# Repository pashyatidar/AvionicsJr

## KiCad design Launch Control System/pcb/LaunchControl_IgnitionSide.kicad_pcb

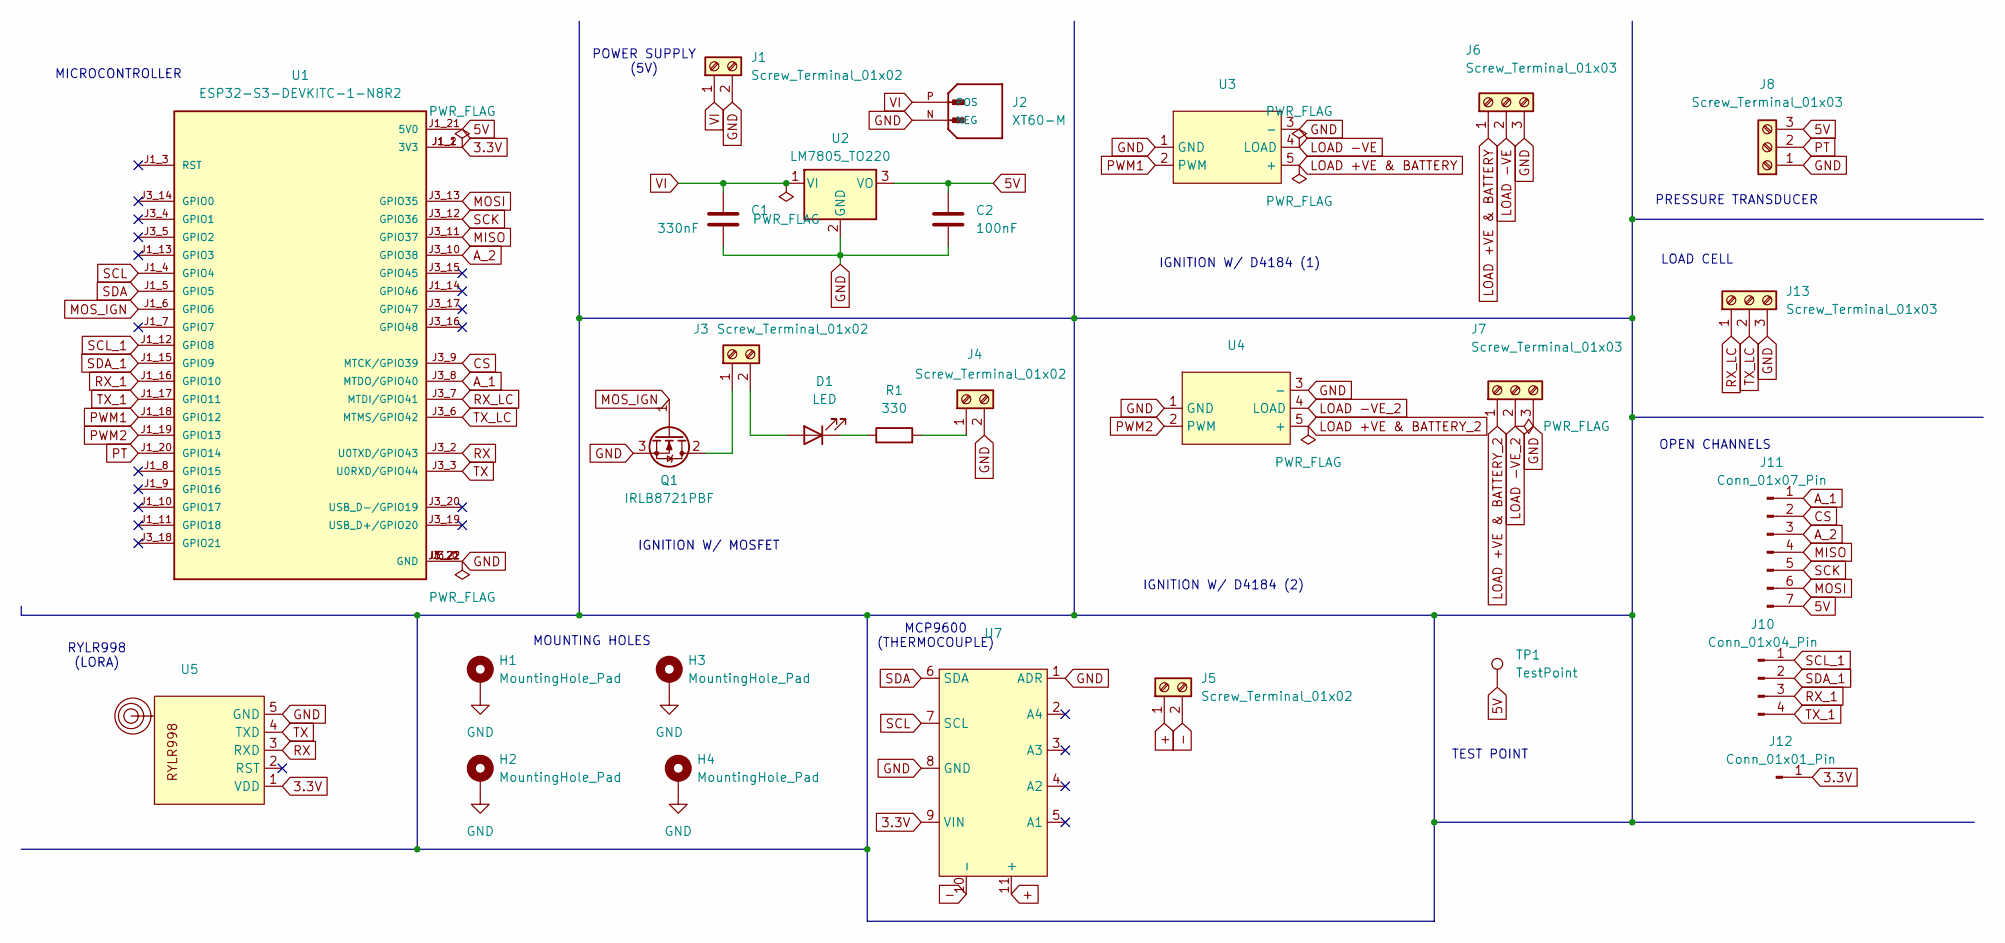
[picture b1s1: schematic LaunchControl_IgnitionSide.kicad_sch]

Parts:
C1: 330nF; C_0805_2012Metric
C2: 100nF; C_0805_2012Metric
D1: LED; LED_0805_2012Metric
H1, H2, H3, H4: MountingHole_Pad; MountingHole_4.3mm_M4_DIN965_Pad
J1, J3, J4, J5: Screw_Terminal_01x02; TerminalBlock_bornier-2_P5.08mm
J2: XT60-M; AMASS_XT60-M; PARTREV V1.2
J6, J7, J8, J13: Screw_Terminal_01x03; TerminalBlock_bornier-3_P5.08mm
J10: Conn_01x04_Pin; PinHeader_1x04_P2.54mm_Vertical
J11: Conn_01x07_Pin; PinHeader_1x07_P2.54mm_Vertical
J12: Conn_01x01_Pin; PinHeader_1x01_P2.54mm_Vertical
Q1: IRLB8721PBF; TO-220-3_Vertical
R1: 330; R_0805_2012Metric
TP1: TestPoint; TestPoint_Loop_D2.60mm_Drill1.6mm_Beaded
U1: ESP32-S3-DEVKITC-1-N8R2; XCVR_ESP32-S3-DEVKITC-1-N8R2; PARTREV V1
U2: LM7805_TO220; TO-220-3_Vertical
U3, U4: D4184
U5: RYLR998
U7: MCP9600

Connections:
3.3V: J12.1, U1.J1_1 (3V3), U1.J1_2 (3V3), U5.1 (VDD), U7.9 (VIN)
5V: C2.2, J8.3, J11.7, TP1.1, U1.J1_21 (5V0), U2.3 (VO)
+: J5.1, U7.11 (+)
-: J5.2, U7.10 (-)
A_1: J11.1, U1.J3_8 (MTDO/GPIO40)
A_2: J11.3, U1.J3_10 (GPIO38)
CS: J11.2, U1.J3_9 (MTCK/GPIO39)
GND: C1.1, C2.1, H1.1, H2.1, H3.1, H4.1, J1.2, J2.N (NEG), J4.2, J6.3, J7.3, J8.1, J13.3, Q1.3 (S), U1.J1_22 (GND), U1.J3_1 (GND), U1.J3_21 (GND), U1.J3_22 (GND), U2.2 (GND), U3.1 (GND), U3.3 (-), U4.1 (GND), U4.3 (-), U5.5 (GND), U7.1 (ADR), U7.8 (GND)
LOAD +VE & BATTERY: J6.1, U3.5 (+)
LOAD +VE & BATTERY_2: J7.1, U4.5 (+)
LOAD -VE: J6.2, U3.4 (LOAD)
LOAD -VE_2: J7.2, U4.4 (LOAD)
MISO: J11.4, U1.J3_11 (GPIO37)
MOSI: J11.6, U1.J3_13 (GPIO35)
MOS_IGN: Q1.1 (G), U1.J1_6 (GPIO6)
unnamed: D1.2 (A), J3.2
unnamed: D1.1 (K), R1.1
unnamed: J3.1, Q1.2 (D)
unnamed: J4.1, R1.2
PT: J8.2, U1.J1_20 (GPIO14)
PWM1: U1.J1_18 (GPIO12), U3.2 (PWM)
PWM2: U1.J1_19 (GPIO13), U4.2 (PWM)
RX: U1.J3_2 (U0TXD/GPIO43), U5.3 (RXD)
RX_1: J10.3, U1.J1_16 (GPIO10)
RX_LC: J13.1, U1.J3_7 (MTDI/GPIO41)
SCK: J11.5, U1.J3_12 (GPIO36)
SCL: U1.J1_4 (GPIO4), U7.7 (SCL)
SCL_1: J10.1, U1.J1_12 (GPIO8)
SDA: U1.J1_5 (GPIO5), U7.6 (SDA)
SDA_1: J10.2, U1.J1_15 (GPIO9)
TX: U1.J3_3 (U0RXD/GPIO44), U5.4 (TXD)
TX_1: J10.4, U1.J1_17 (GPIO11)
TX_LC: J13.2, U1.J3_6 (MTMS/GPIO42)
VI: C1.2, J1.1, J2.P (POS), U2.1 (VI)

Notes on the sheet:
PRESSURE TRANSDUCER
LOAD CELL
IGNITION W/ D4184 (2)
RYLR998 (LORA)
OPEN CHANNELS
IGNITION W/ D4184 (1)
POWER SUPPLY (5V)
IGNITION W/ MOSFET
MOUNTING HOLES
MICROCONTROLLER
MCP9600 (THERMOCOUPLE)
TEST POINT

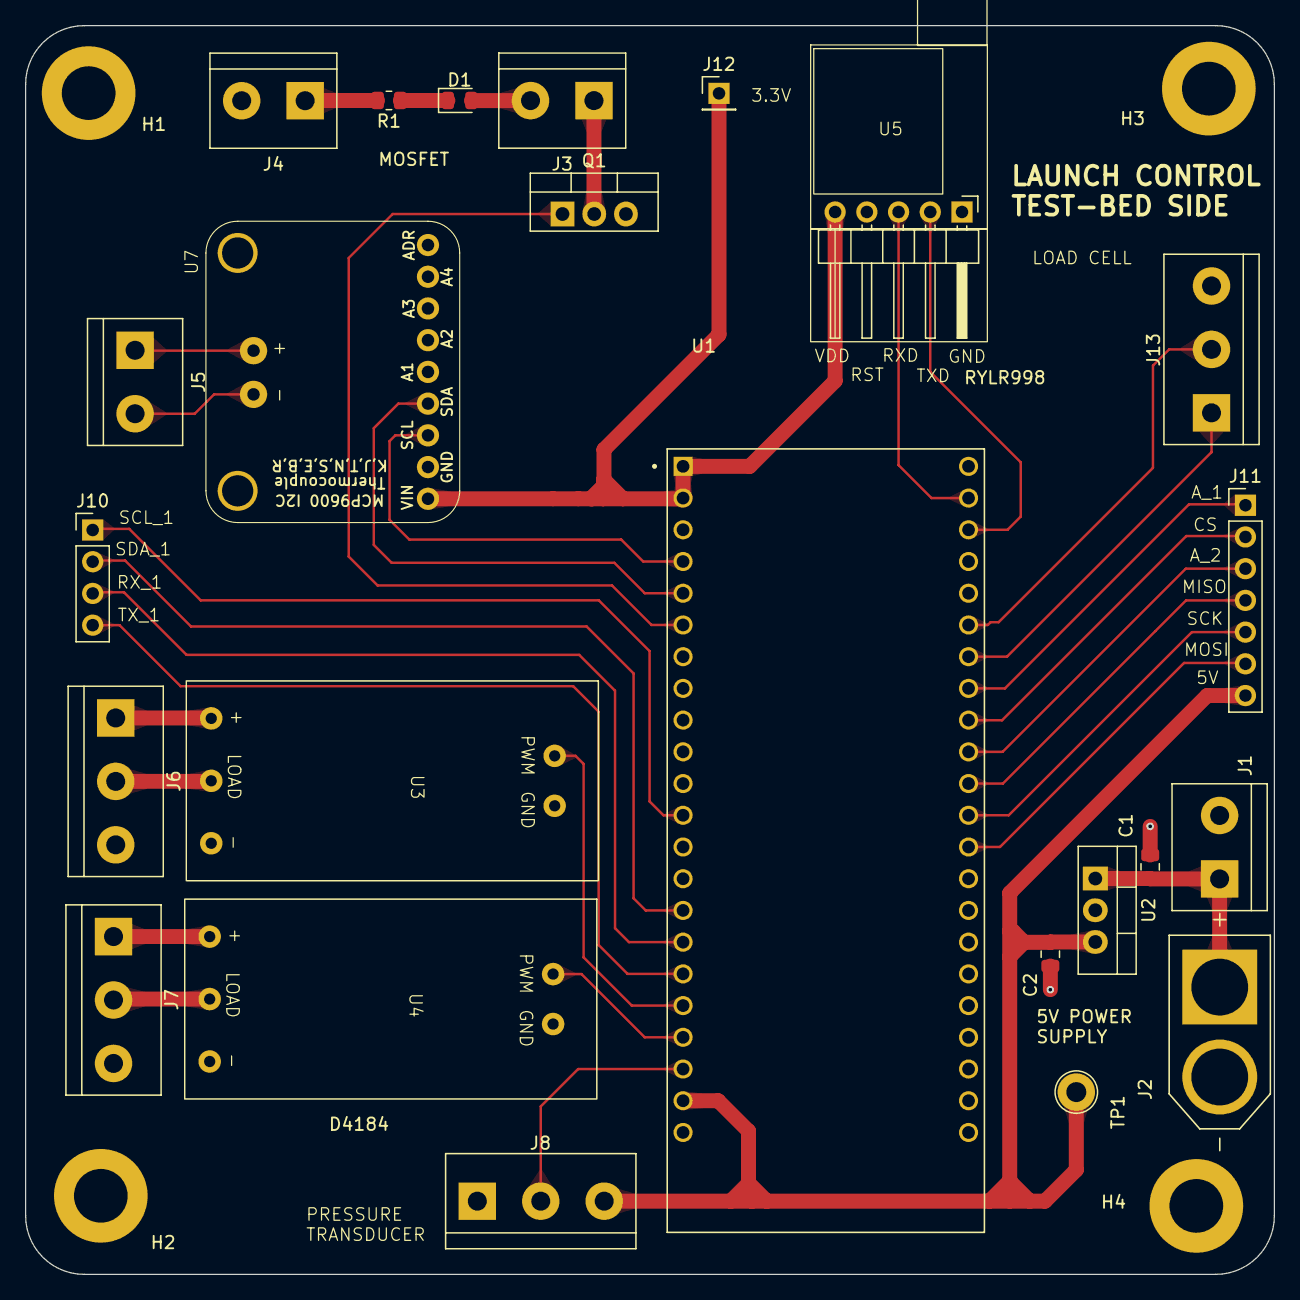
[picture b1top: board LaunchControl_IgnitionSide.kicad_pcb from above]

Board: 2 copper layers, 100.0 x 100.0 mm, 28 parts (0 on the bottom side), 34 nets.

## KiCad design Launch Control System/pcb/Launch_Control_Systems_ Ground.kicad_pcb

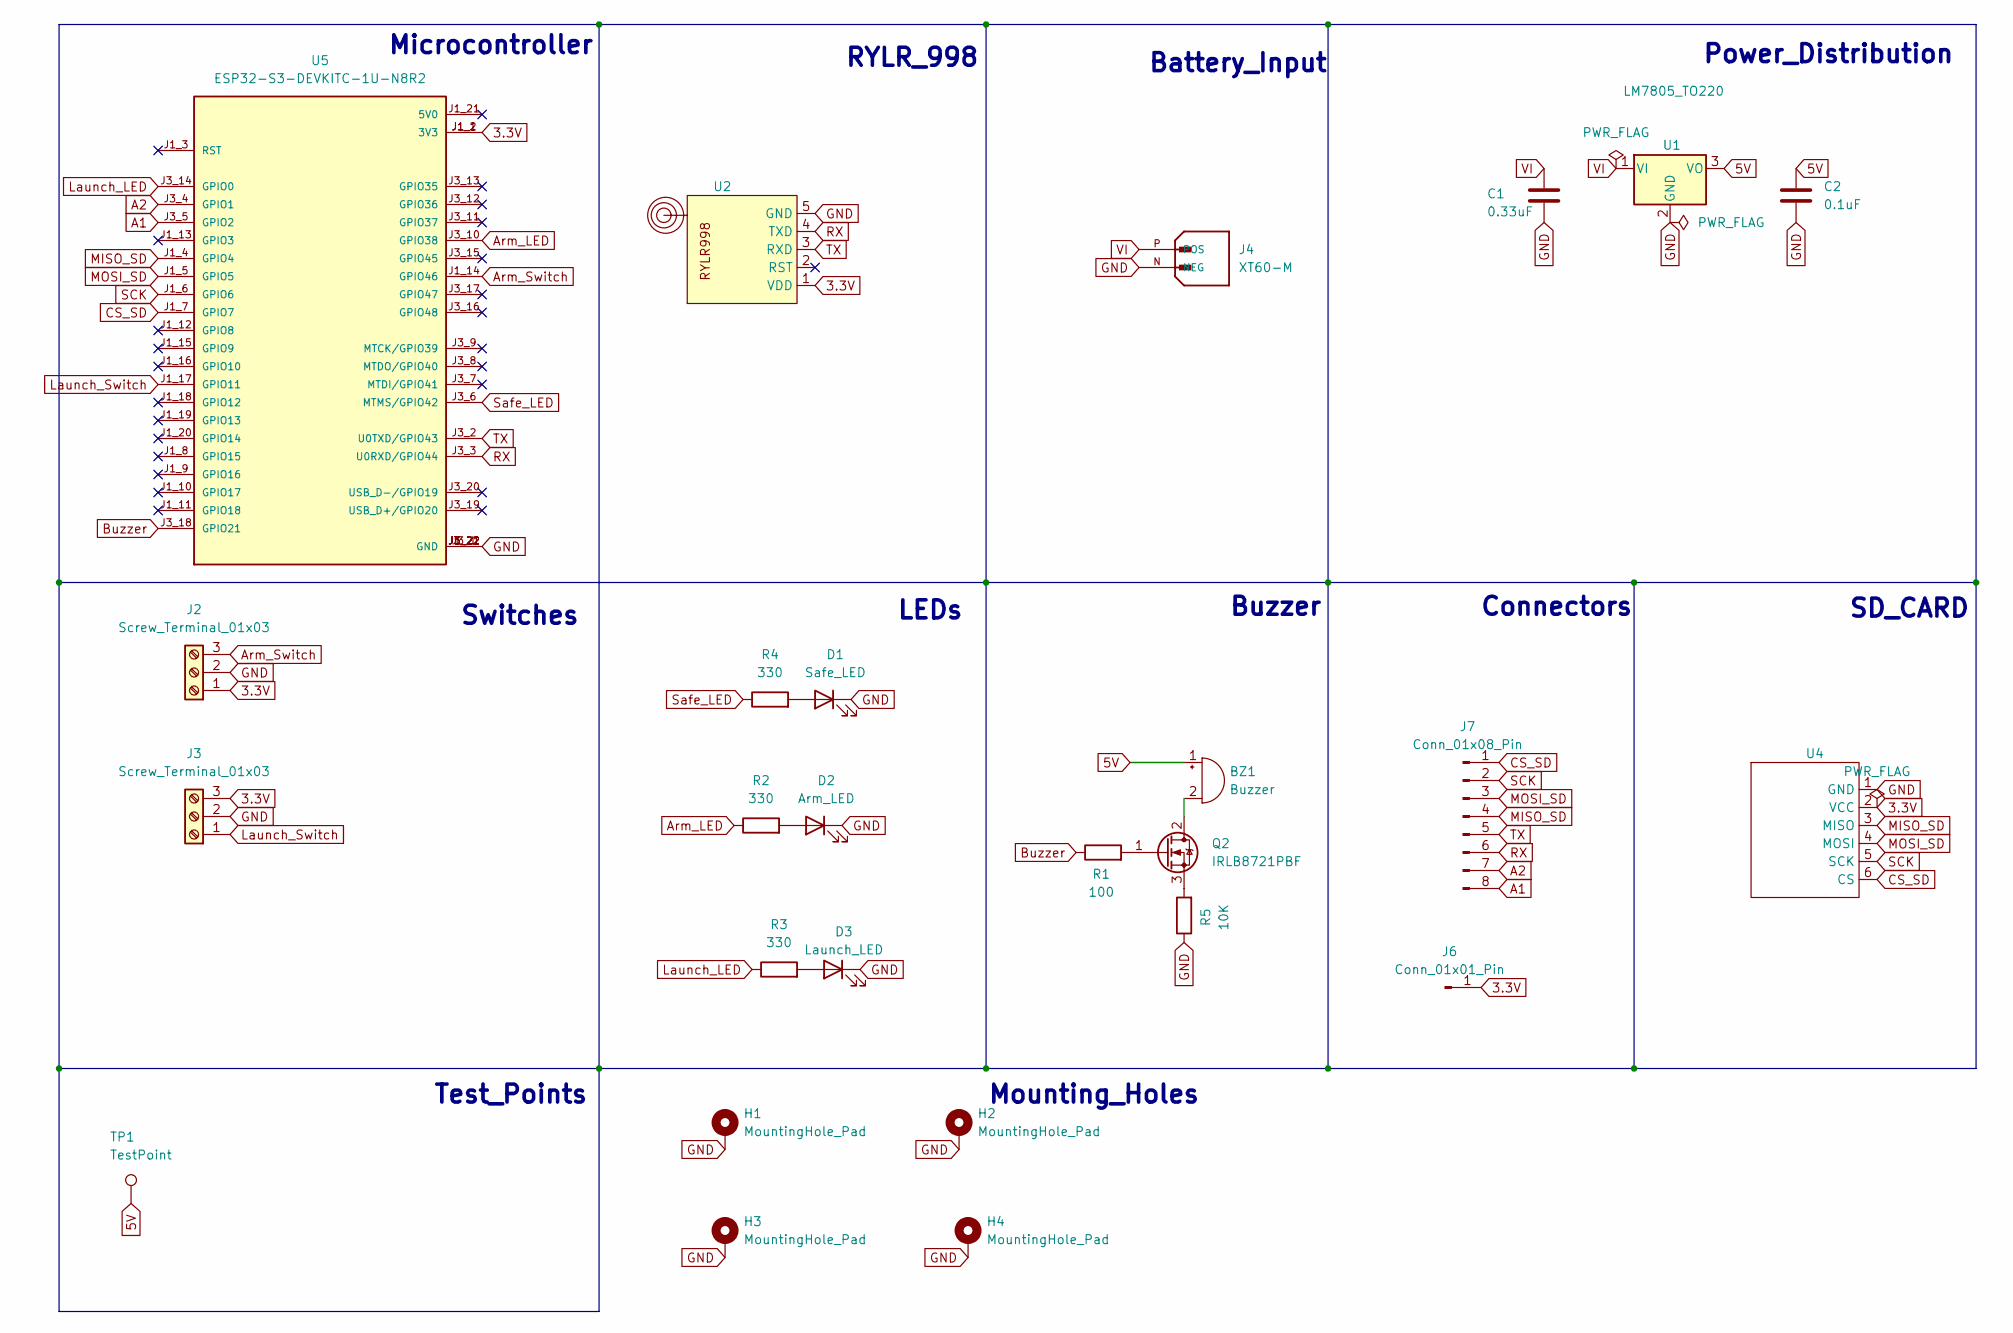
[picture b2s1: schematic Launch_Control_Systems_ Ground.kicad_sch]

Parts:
BZ1: Buzzer; Buzzer_12x9.5RM7.6
C1: 0.33uF; C_0805_2012Metric
C2: 0.1uF; C_0805_2012Metric
D1: Safe_LED; LED_D5.0mm
D2: Arm_LED; LED_D5.0mm
D3: Launch_LED; LED_D5.0mm
H1, H2, H3, H4: MountingHole_Pad; MountingHole_4.3mm_M4_DIN965_Pad
J2, J3: Screw_Terminal_01x03; TerminalBlock_bornier-3_P5.08mm
J4: XT60-M; AMASS_XT60-M; PARTREV V1.2
J6: Conn_01x01_Pin; PinHeader_1x01_P2.54mm_Vertical
J7: Conn_01x08_Pin; PinHeader_1x08_P2.54mm_Vertical
Q2: IRLB8721PBF; TO-220-3_Vertical
R1: 100; R_0805_2012Metric
R2, R3, R4: 330; R_0805_2012Metric
R5: 10K; R_0805_2012Metric
TP1: TestPoint; TestPoint_Loop_D2.60mm_Drill1.6mm_Beaded
U1: LM7805_TO220; TO-220-3_Vertical
U2: RYLR_998_SKT
U4: SD card reader 2
U5: ESP32-S3-DEVKITC-1U-N8R2; XCVR_ESP32-S3-DEVKITC-1U-N8R2

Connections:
3.3V: J2.1, J3.3, J6.1, U2.1 (VDD), U4.2 (VCC), U5.J1_1 (3V3), U5.J1_2 (3V3)
5V: BZ1.1 (+), C2.1, TP1.1, U1.3 (VO)
A1: J7.8, U5.J3_5 (GPIO2)
A2: J7.7, U5.J3_4 (GPIO1)
Arm_LED: R2.1, U5.J3_10 (GPIO38)
Arm_Switch: J2.3, U5.J1_14 (GPIO46)
Buzzer: R1.1, U5.J3_18 (GPIO21)
CS_SD: J7.1, U4.6 (CS), U5.J1_7 (GPIO7)
GND: C1.2, C2.2, D1.1 (K), D2.1 (K), D3.1 (K), H1.1, H2.1, H3.1, H4.1, J2.2, J3.2, J4.N (NEG), R5.1, U1.2 (GND), U2.5 (GND), U4.1 (GND), U5.J1_22 (GND), U5.J3_1 (GND), U5.J3_21 (GND), U5.J3_22 (GND)
Launch_LED: R3.1, U5.J3_14 (GPIO0)
Launch_Switch: J3.1, U5.J1_17 (GPIO11)
MISO_SD: J7.4, U4.3 (MISO), U5.J1_4 (GPIO4)
MOSI_SD: J7.3, U4.4 (MOSI), U5.J1_5 (GPIO5)
unnamed: BZ1.2 (-), Q2.2 (D)
unnamed: D1.2 (A), R4.2
unnamed: D2.2 (A), R2.2
unnamed: D3.2 (A), R3.2
unnamed: Q2.1 (G), R1.2
unnamed: Q2.3 (S), R5.2
RX: J7.6, U2.4 (TXD), U5.J3_3 (U0RXD/GPIO44)
SCK: J7.2, U4.5 (SCK), U5.J1_6 (GPIO6)
Safe_LED: R4.1, U5.J3_6 (MTMS/GPIO42)
TX: J7.5, U2.3 (RXD), U5.J3_2 (U0TXD/GPIO43)
VI: C1.1, J4.P (POS), U1.1 (VI)

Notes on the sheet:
Test_Points
Connectors
SD_CARD
RYLR_998
LEDs
Microcontroller
Switches
Power_Distribution
Battery_Input
Mounting_Holes
Buzzer

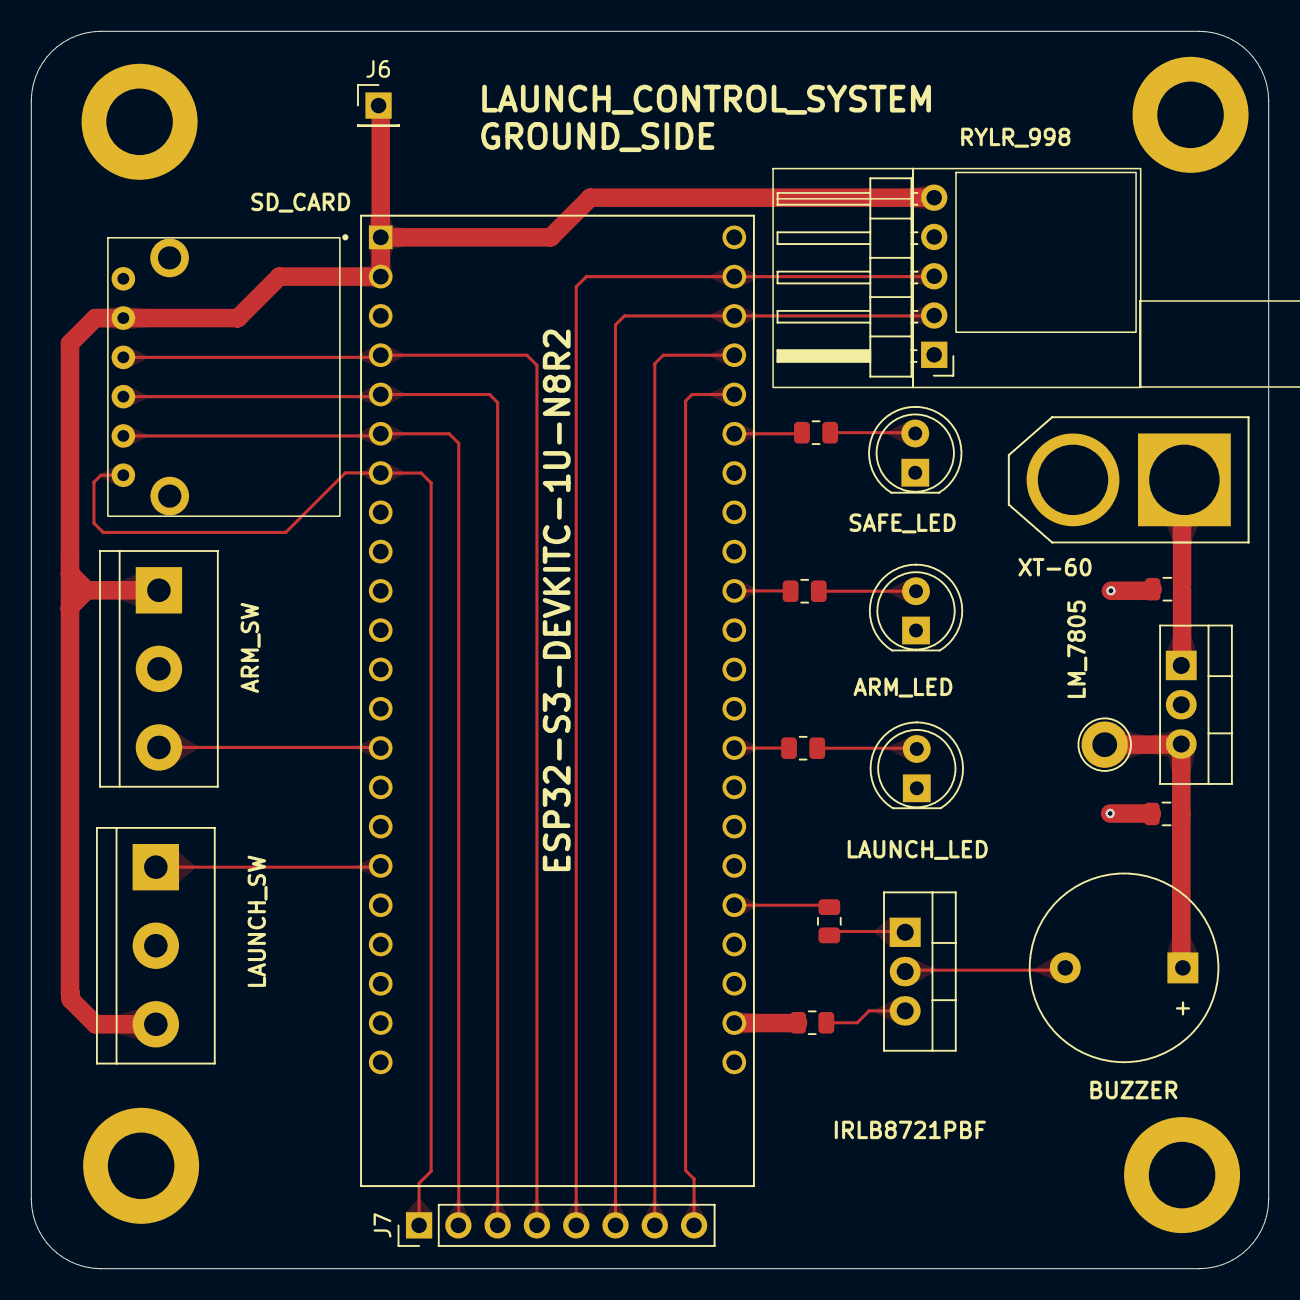
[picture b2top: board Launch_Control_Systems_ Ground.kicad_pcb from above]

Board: 2 copper layers, 80.0 x 80.0 mm, 26 parts (0 on the bottom side), 24 nets.

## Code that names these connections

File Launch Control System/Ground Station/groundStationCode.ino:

#include <SD.h>
#include <freertos/FreeRTOS.h>
#include <freertos/task.h>
#include <freertos/semphr.h>

SemaphoreHandle_t logMutex;


#define BUZZER_PIN 38
#define RX_RYLR 44
#define TX_RYLR 43
#define ARM_SW 4
#define LCH_SW 5
//#define SAFE_SW 6

#define ARM_LED 17
#define LAUNCH_LED 16
#define SAFE_LED 18

HardwareSerial RYLR(1);


typedef enum {
  SAFE,
  ARMED,
  LAUNCHED
} STATE;
STATE currentState =SAFE;

File logFile;
String message, response;
static int safeFlag = 0, armFlag = 0, launchFlag = 0;

String parseRYLR(String input) {
  int start = input.indexOf(',') + 1;
  start = input.indexOf(',', start) + 1;
  int end = input.indexOf(',', start);
  String parsed = input.substring(start, end);
  parsed.trim();
  return parsed;
}

void sendState(String data) {
  Serial.println("TRANSMIT: " + data);
  message = "AT+SEND=0," + String(data.length()) + "," + data + "\r\n";
  RYLR.flush();
  RYLR.print(message);
  vTaskDelay(10);
}


bool allSwitchesLow() {
  return digitalRead(ARM_SW) == LOW && digitalRead(LCH_SW) == LOW;
}

void buzz(void *pvParameters) {
  pinMode(BUZZER_PIN, OUTPUT);
  digitalWrite(BUZZER_PIN, HIGH);
  vTaskDelay(pdMS_TO_TICKS(200));
  digitalWrite(BUZZER_PIN, LOW);
  vTaskDelay(pdMS_TO_TICKS(800));

  vTaskDelete(NULL);
}

void fsm(void *pvParameters) {

  for (;;) {
    switch (currentState) {
  
      case SAFE:
        digitalWrite(SAFE_LED, HIGH);
        if (digitalRead(ARM_SW) == HIGH && digitalRead(LCH_SW) == LOW) {
          if (safeFlag == 0) {
            sendState("ARM");
            vTaskDelay(pdMS_TO_TICKS(500));
            safeFlag = 1;
            armFlag = 0;
            digitalWrite(ARM_LED, HIGH);
            digitalWrite(SAFE_LED, LOW);
            currentState = ARMED;
            xTaskCreatePinnedToCore(buzz, "Buzz", 128, NULL, 3, NULL, 0);
          }
        }
        break;
      case ARMED:
        if (digitalRead(ARM_SW) == LOW) {
          if (armFlag == 0) {
            sendState("DISARM");
            vTaskDelay(pdMS_TO_TICKS(500));
            armFlag = 1;
            safeFlag = 0;
          }
        } else if ( digitalRead(LCH_SW) == HIGH && digitalRead(ARM_SW) == HIGH) {
          if (launchFlag == 0) {
            sendState("LAUNCH");
            vTaskDelay(pdMS_TO_TICKS(500));
            launchFlag = 1;
            currentState = LAUNCHED;
            digitalWrite(LAUNCH_LED, HIGH);
            digitalWrite(ARM_LED, LOW);
            digitalWrite(SAFE_LED, LOW);
            xTaskCreatePinnedToCore(buzz, "Buzz", 128, NULL, 3, NULL, 0);
          }
        }
        break;
      case LAUNCHED:
        xTaskCreatePinnedToCore(buzz, "Buzz", 128, NULL, 3, NULL, 0);
        for (int i = 0; i < 3; i++) {
          digitalWrite(LAUNCH_LED, HIGH);
          digitalWrite(ARM_LED, HIGH);
          digitalWrite(SAFE_LED, HIGH);

          vTaskDelay(500);

          digitalWrite(LAUNCH_LED, LOW);
          digitalWrite(ARM_LED, LOW);
          digitalWrite(SAFE_LED, LOW);

          vTaskDelay(500);
        }

        digitalWrite(LAUNCH_LED, LOW);
        digitalWrite(ARM_LED, LOW);
        digitalWrite(SAFE_LED, LOW);

        break;
      default:
        Serial.println("ERROR: Unknown state. Resetting to OFF.");
        currentState = SAFE;
        sendState("SAFE");
        digitalWrite(SAFE_LED, HIGH);
        digitalWrite(ARM_LED, LOW);
        digitalWrite(LAUNCH_LED, LOW);
        break;
    }
    vTaskDelay(pdMS_TO_TICKS(50));
  }
}

void checkTestBed(void *pvParameters) {
  for (;;) {
    if (RYLR.available()) {
      response = RYLR.readStringUntil('\n');
      response = parseRYLR(response);
      if (response.length() > 3) {
        Serial.println(response);
        if (xSemaphoreTake(logMutex, portMAX_DELAY)) {
          logFile = SD.open("loadcell.txt", FILE_WRITE);
          if (logFile) {
            logFile.println(response);
            logFile.close();
          }
          xSemaphoreGive(logMutex);
        }
      }
    }
    if (response.equals("TESTBED STATE: SAFE")) {
      currentState = SAFE;
      Serial.println("GROUND STATE: SAFE");
    } else if (response.equals("TESTBED STATE: ARMED")) {
      currentState = ARMED;
      Serial.println("GROUND STATE: ARMED");
    } else if (response.equals("TESTBED STATE: LAUNCHED")) {
      currentState = LAUNCHED;
      Serial.println("GROUND STATE: LAUNCHED");
    }
    if (response.length() > 3) {
      //Serial.println(response);
    }
    vTaskDelay(pdMS_TO_TICKS(100));
  }
}

void setup() {
  Serial.begin(9600);
  RYLR.begin(57600, SERIAL_8N1, RX_RYLR, TX_RYLR);
  pinMode(ARM_LED, OUTPUT);
  pinMode(SAFE_LED, OUTPUT);
  pinMode(LAUNCH_LED, OUTPUT);
  pinMode(ARM_SW, INPUT);
  pinMode(LCH_SW, INPUT);
  //pinMode(SAFE_SW, INPUT);
  pinMode(BUZZER_PIN, OUTPUT);
  digitalWrite(BUZZER_PIN, LOW);


  logMutex = xSemaphoreCreateMutex();
  if (logMutex == NULL) {
    Serial.println("failed to create SD CARD Index ");
    while (1)
      ;
  }
  xTaskCreatePinnedToCore(fsm, "FSM", 512, NULL, 2, NULL, 0);
  xTaskCreatePinnedToCore(checkTestBed, "CheckTestBed", 1024, NULL, 1, NULL, 1);

  Serial.println("\nSerial Comm. Initialised.");
  if (!SD.begin()) {
    Serial.println("SD card initialisation failed.");
  }

  logFile = SD.open("loadcell.txt", FILE_WRITE);
  if (!logFile) {
    Serial.println("Couldn't open log file");
  } else {
    Serial.println("Logging to SD card...");
    logFile.close();
  }

  Serial.println("GROUNDSTATION SET UP COMPLETE.");
}




void loop() {}

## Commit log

2025-03-29 Create xyz
2025-03-29 Create PID controller
    Test Code
2025-03-29 Add files via upload
    PID controller Test Code
2025-03-29 Add files via upload
    Fuzzzzy controller test code
2025-03-29 PIFlashinfo.ino
2025-06-22 testBedSiteCode.ino
2025-07-08 Pending changes exported from your codespace
2025-08-23 site.css
2025-08-23 index.html
2025-08-23 Create Plotter
